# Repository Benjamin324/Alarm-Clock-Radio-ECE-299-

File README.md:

# ECE 299 Design Project
## University of Victoria

This is a design project for ECE 299, Introduction to Electrical Engineering Design, at the University of Victoria.

The goal of this design course is to prototype, develop, and manufacture a clock radio based on the Raspberry Pi Pico. Design elements include Python code running on the RPi, KiCAD schematic and PCB design, and SolidWorks enclosure design.

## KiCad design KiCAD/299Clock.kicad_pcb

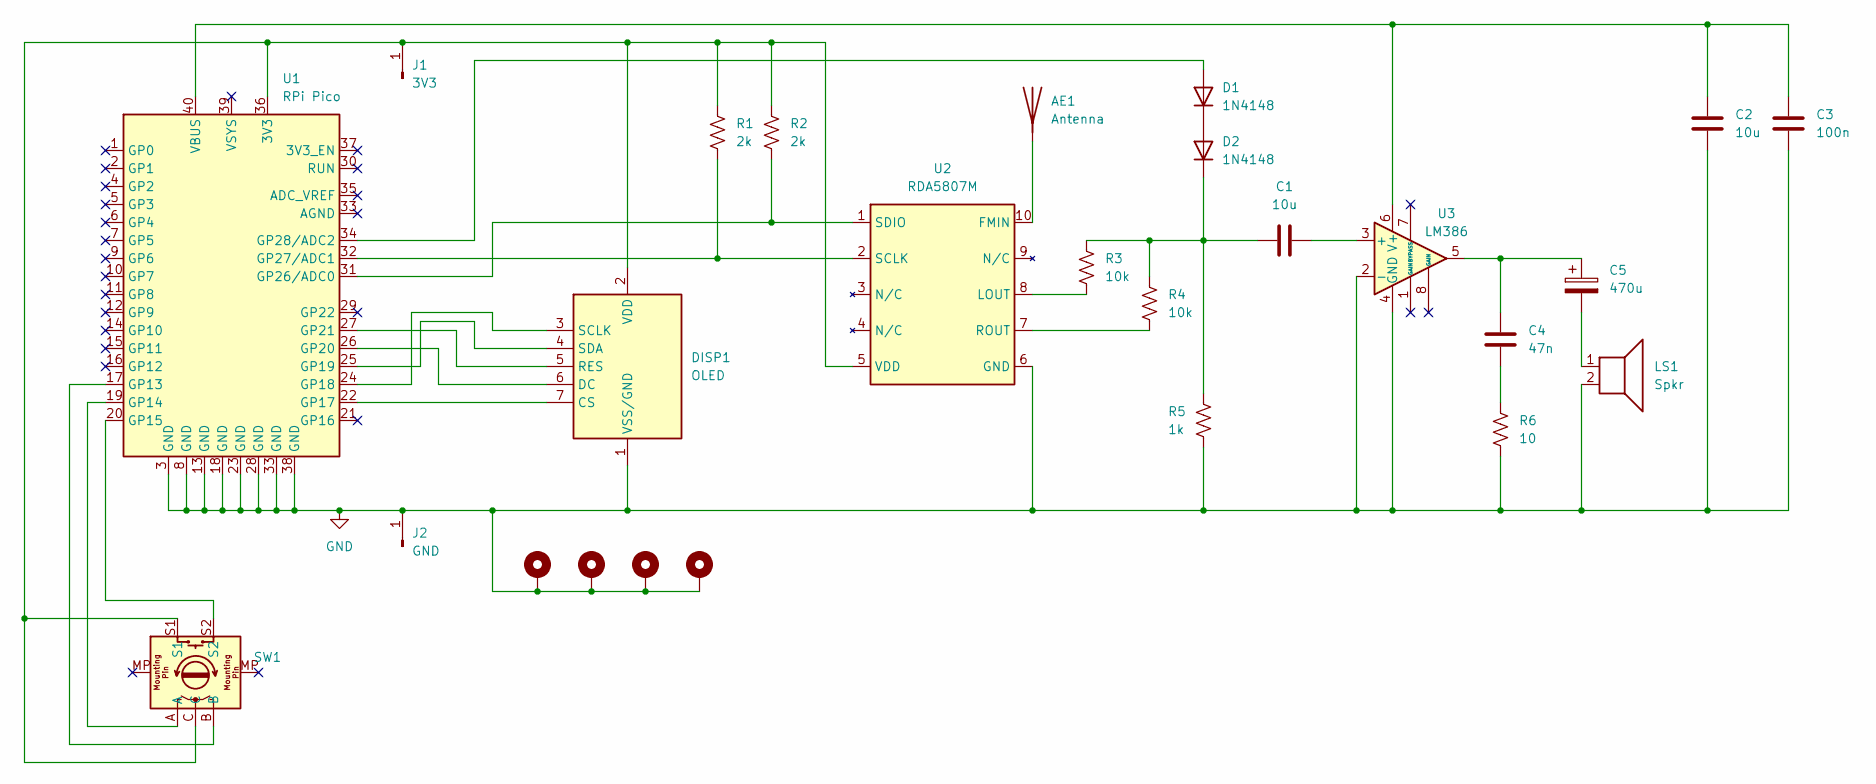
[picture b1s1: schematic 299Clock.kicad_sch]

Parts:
AE1: Antenna; SolderWire-0.1sqmm_1x01_D0.4mm_OD1mm
C1, C2: 10u; C_Rect_L7.0mm_W2.5mm_P5.00mm
C3: 100n; C_Rect_L7.0mm_W2.5mm_P5.00mm
C4: 47n; C_Rect_L7.0mm_W2.5mm_P5.00mm
C5: 470u; CP_Radial_D5.0mm_P2.50mm
D1, D2: 1N4148; D_DO-35_SOD27_P7.62mm_Horizontal
DISP1: OLED; PinHeader_1x07_P2.54mm_Vertical
H1, H2, H3, H4: MountingHole_Pad; MountingHole_3.2mm_M3_DIN965_Pad_TopBottom
J1: 3V3; SolderWire-0.1sqmm_1x01_D0.4mm_OD1mm
J2: GND; SolderWire-0.1sqmm_1x01_D0.4mm_OD1mm
LS1: Spkr; SolderWire-0.1sqmm_1x02_P3.6mm_D0.4mm_OD1mm
R1, R2: 2k; R_Axial_DIN0207_L6.3mm_D2.5mm_P7.62mm_Horizontal
R3, R4: 10k; R_Axial_DIN0207_L6.3mm_D2.5mm_P7.62mm_Horizontal
R5: 1k; R_Axial_DIN0207_L6.3mm_D2.5mm_P7.62mm_Horizontal
R6: 10; R_Axial_DIN0207_L6.3mm_D2.5mm_P7.62mm_Horizontal
SW1: PEC11R; PinHeader_1x05_P2.54mm_Vertical
U1: RPi Pico; RPi_Pico_TH
U2: RDA5807M; RDA5807M_Module_TH
U3: LM386; DIP-8_W7.62mm

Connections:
GND: C2.2, C3.2, DISP1.1 (VSS/GND), H1.1, H2.1, H3.1, H4.1, J2.1, LS1.2, R5.2, R6.2, U1.3 (GND), U1.8 (GND), U1.13 (GND), U1.18 (GND), U1.23 (GND), U1.28 (GND), U1.33 (GND), U1.38 (GND), U2.6 (GND), U3.2 (-), U3.4 (GND); also elsewhere on the board
unnamed: AE1.1 (A), U2.10 (FMIN)
unnamed: C1.1, D2.1 (K), R3.1, R4.1, R5.1
unnamed: C1.2, U3.3 (+)
unnamed: C2.1, C3.1, U1.40 (VBUS), U3.6 (V+)
unnamed: C4.1, C5.1, U3.5
unnamed: C4.2, R6.1
unnamed: C5.2, LS1.1
unnamed: D1.1 (K), D2.2 (A)
unnamed: D1.2 (A), U1.34 (GP28/ADC2)
unnamed 10: DISP1.2 (VDD), J1.1, R1.1, R2.1, SW1.C, SW1.S1, U1.36 (3V3), U2.5 (VDD); also elsewhere on the board
unnamed: DISP1.3 (SCLK), U1.24 (GP18)
unnamed: DISP1.4 (SDA), U1.25 (GP19)
unnamed: DISP1.5 (RES), U1.27 (GP21)
unnamed: DISP1.6 (DC), U1.26 (GP20)
unnamed: DISP1.7 (CS), U1.22 (GP17)
unnamed: R1.2, U1.32 (GP27/ADC1), U2.2 (SCLK)
unnamed: R2.2, U1.31 (GP26/ADC0), U2.1 (SDIO)
unnamed: R3.2, U2.8 (LOUT)
unnamed: R4.2, U2.7 (ROUT)
unnamed: SW1.A, U1.19 (GP14)
unnamed: SW1.B, U1.17 (GP13)
unnamed: SW1.S2, U1.20 (GP15)

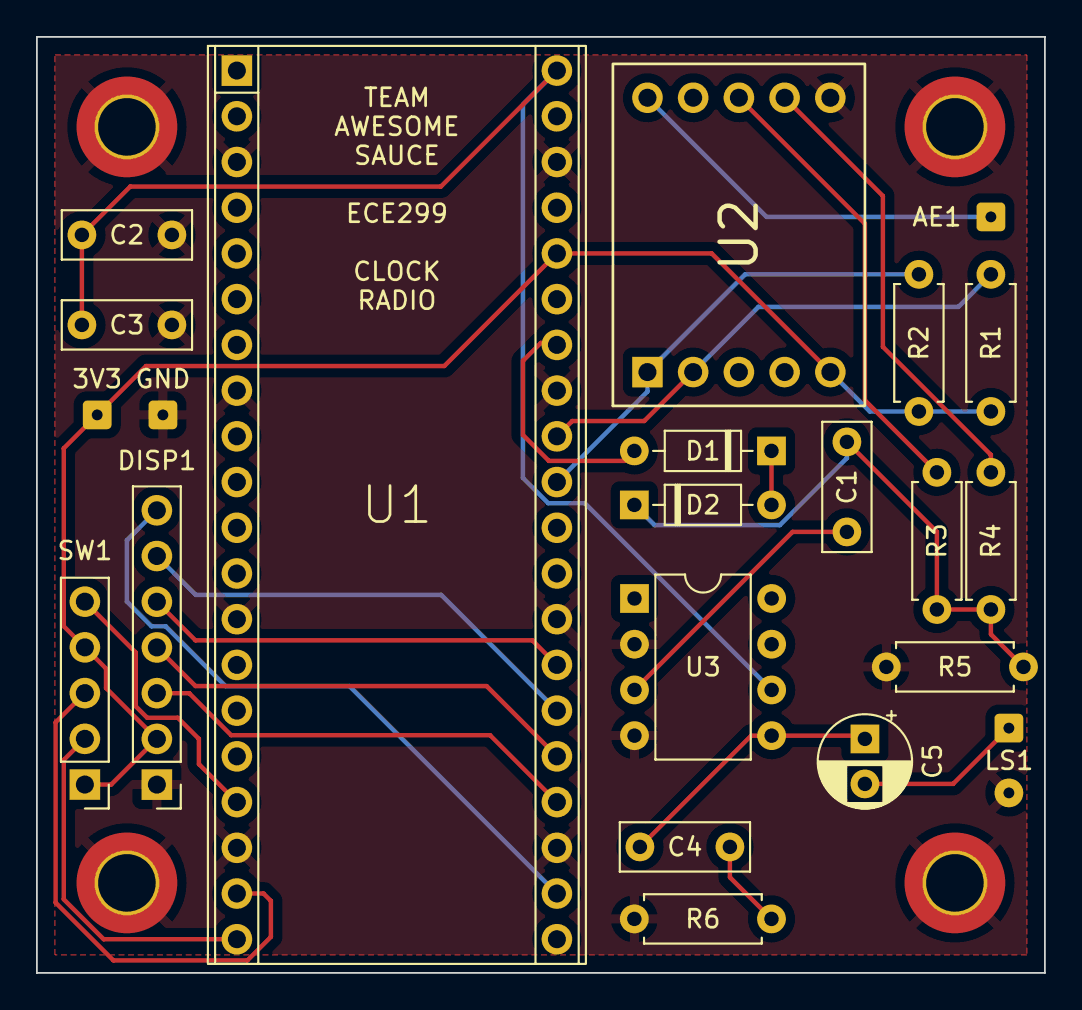
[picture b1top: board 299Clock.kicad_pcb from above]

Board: 2 copper layers, 56.0 x 52.0 mm, 26 parts (0 on the bottom side), 23 nets.

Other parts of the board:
3V3: 3V3; SolderWire-0.1sqmm_1x01_D0.4mm_OD1mm
GND: GND; SolderWire-0.1sqmm_1x01_D0.4mm_OD1mm

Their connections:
GND: GND.1; also elsewhere on the board
unnamed 10: 3V3.1; also elsewhere on the board

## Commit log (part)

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2026-06-06 Initial functionality
2026-06-06 added module for continuos items
2026-06-06 Added font size library
2026-06-06 Implemented secondary time and Volume bar
2026-06-06 minmal encoder functionality'
2026-06-06 stuff
2026-06-11 Add files via upload
    New script for managing Interrupt Requests and control over the UI. This code will be more compatible between a button interface and a rotary encoder
2026-06-12 Add files via upload
    newer revision
2026-06-20 Rename button_ui.py to Clock-script_consolidated.py
2026-06-20 Updated KiCAD files
2026-06-20 Creating new KiCAD folder
2026-06-20 Rename 299Clock_v2.kicad_pro to KiCAD/299Clock.kicad_pro
2026-06-20 Rename 299Clock_v2.kicad_prl to 299Clock.kicad_prl
2026-06-20 Update README.md for grammar
2026-06-24 Added test points to PCB
2026-06-24 Began adding traces to PCB
2026-06-24 Finished traces, routed sw, add ground planes
